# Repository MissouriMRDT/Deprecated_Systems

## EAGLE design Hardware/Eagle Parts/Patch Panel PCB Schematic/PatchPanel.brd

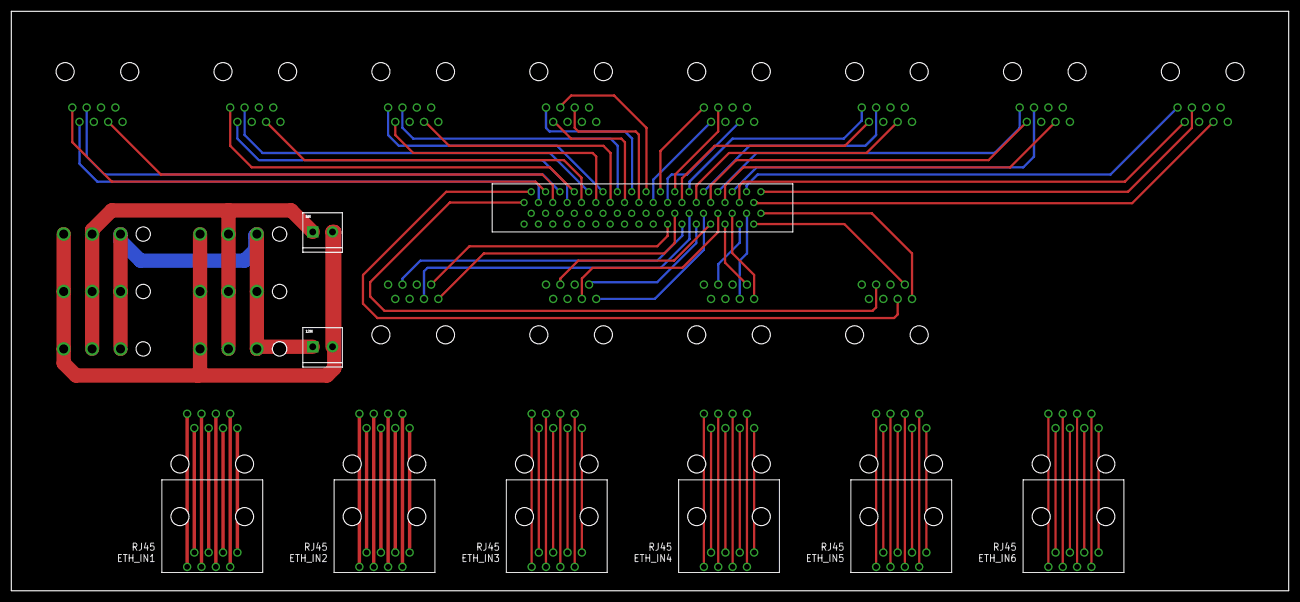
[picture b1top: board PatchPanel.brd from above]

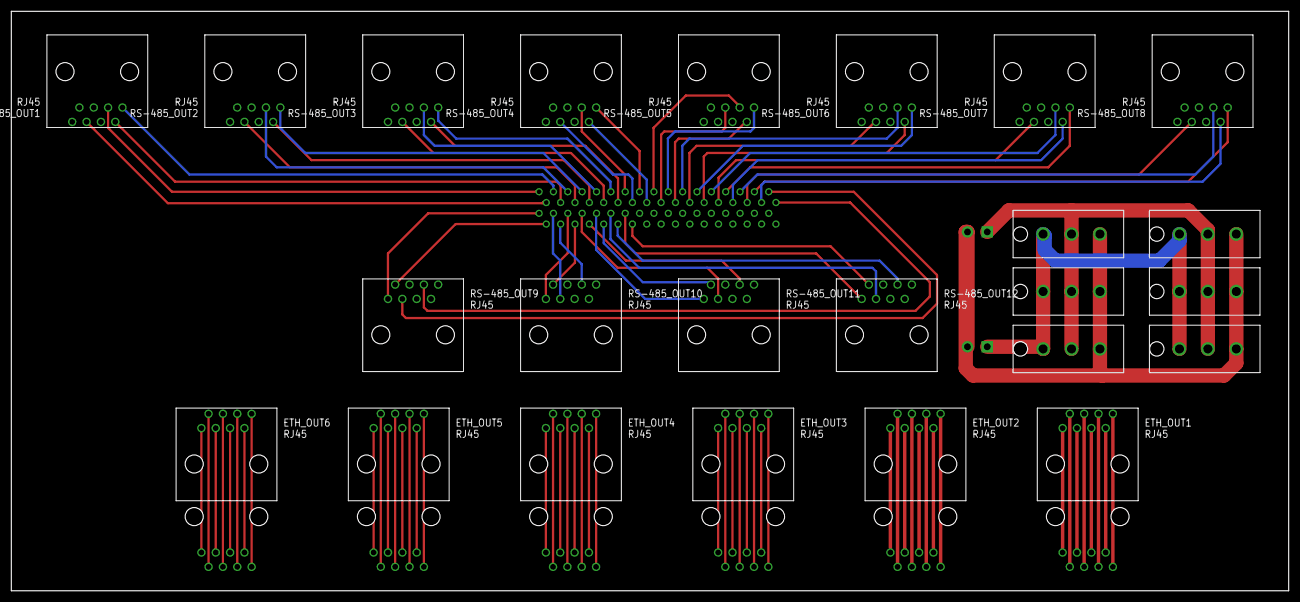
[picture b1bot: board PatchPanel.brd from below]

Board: 2 copper layers, 226.0 x 102.5 mm, 33 parts (24 on the bottom side), 99 nets.

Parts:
5IN, 12IN: M023.5MM; SCREWTERMINAL-3.5MM-2
ETH_IN1, ETH_IN2, ETH_IN3, ETH_IN4, ETH_IN5, ETH_IN6: RJ45; RJ45-CAT5E
ETH_OUT1, ETH_OUT2, ETH_OUT3, ETH_OUT4, ETH_OUT5, ETH_OUT6: RJ45; RJ45-CAT5E
RS-485_OUT1, RS-485_OUT2, RS-485_OUT3, RS-485_OUT4, RS-485_OUT5, RS-485_OUT6, RS-485_OUT7, RS-485_OUT8, RS-485_OUT9, RS-485_OUT10, RS-485_OUT11, RS-485_OUT12: RJ45; RJ45-CAT5E
U$1: TB60050685100; 60050685100
U$2, U$3, U$4, U$5, U$6, U$7: 3PIN; 0.93"

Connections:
1_RX+: RS-485_OUT1.1, U$1.3
1_RX-: RS-485_OUT1.2, U$1.4
1_TX+: RS-485_OUT1.3, U$1.1
1_TX-: RS-485_OUT1.6, U$1.2
2_RX+: RS-485_OUT2.1, U$1.7
2_RX-: RS-485_OUT2.2, U$1.8
2_TX+: RS-485_OUT2.3, U$1.5
2_TX-: RS-485_OUT2.6, U$1.6
3_RX+: RS-485_OUT3.1, U$1.11
3_RX-: RS-485_OUT3.2, U$1.12
3_TX+: RS-485_OUT3.3, U$1.9
3_TX-: RS-485_OUT3.6, U$1.10
4_RX+: RS-485_OUT4.1, U$1.15
4_RX-: RS-485_OUT4.2, U$1.16
4_TX+: RS-485_OUT4.3, U$1.13
4_TX-: RS-485_OUT4.6, U$1.14
5_RX+: RS-485_OUT5.1, U$1.19
5_RX-: RS-485_OUT5.2, U$1.20
5_TX+: RS-485_OUT5.3, U$1.17
5_TX-: RS-485_OUT5.5, U$1.18
6_RX+: RS-485_OUT6.1, U$1.23
6_RX-: RS-485_OUT6.2, U$1.24
6_TX+: RS-485_OUT6.3, U$1.21
6_TX-: RS-485_OUT6.6, U$1.22
7_RX+: RS-485_OUT7.1, U$1.27
7_RX-: RS-485_OUT7.2, U$1.28
7_TX+: RS-485_OUT7.3, U$1.25
7_TX-: RS-485_OUT7.6, U$1.26
8_RX+: RS-485_OUT8.1, U$1.31
8_RX-: RS-485_OUT8.2, U$1.32
8_TX+: RS-485_OUT8.3, U$1.29
8_TX-: RS-485_OUT8.6, U$1.30
9_RX+: RS-485_OUT9.1, U$1.35
9_RX-: RS-485_OUT9.2, U$1.36
9_TX+: RS-485_OUT9.3, U$1.33
9_TX-: RS-485_OUT9.6, U$1.34
10_RX+: RS-485_OUT10.1, U$1.39
10_RX-: RS-485_OUT10.2, U$1.40
10_TX+: RS-485_OUT10.3, U$1.37
10_TX-: RS-485_OUT10.6, U$1.38
11_RX+: RS-485_OUT11.1, U$1.43
11_RX-: RS-485_OUT11.2, U$1.44
11_TX+: RS-485_OUT11.3, U$1.41
11_TX-: RS-485_OUT11.6, U$1.42
12_RX+: RS-485_OUT12.1, U$1.47
12_RX-: RS-485_OUT12.2, U$1.48
12_TX+: RS-485_OUT12.3, U$1.45
12_TX-: RS-485_OUT12.6, U$1.46
+5V: 5IN.1, U$2.2, U$3.2, U$4.2, U$5.2, U$6.2, U$7.2
+12V: 12IN.1, U$2.1, U$3.1, U$4.1, U$5.1, U$6.1, U$7.1
GND: 5IN.2, 12IN.2, U$2.3, U$3.3, U$4.3, U$5.3, U$6.3, U$7.3
unnamed: ETH_IN1.1, ETH_OUT1.1
unnamed: ETH_IN1.2, ETH_OUT1.2
unnamed: ETH_IN1.3, ETH_OUT1.3
unnamed: ETH_IN1.4, ETH_OUT1.4
unnamed: ETH_IN1.5, ETH_OUT1.5
unnamed: ETH_IN1.6, ETH_OUT1.6
unnamed: ETH_IN1.7, ETH_OUT1.7
unnamed: ETH_IN1.8, ETH_OUT1.8
unnamed: ETH_IN2.1, ETH_OUT2.1
unnamed: ETH_IN2.2, ETH_OUT2.2
unnamed: ETH_IN2.3, ETH_OUT2.3
unnamed: ETH_IN2.4, ETH_OUT2.4
unnamed: ETH_IN2.5, ETH_OUT2.5
unnamed: ETH_IN2.6, ETH_OUT2.6
unnamed: ETH_IN2.7, ETH_OUT2.7
unnamed: ETH_IN2.8, ETH_OUT2.8
unnamed: ETH_IN3.1, ETH_OUT3.1
unnamed: ETH_IN3.2, ETH_OUT3.2
unnamed: ETH_IN3.3, ETH_OUT3.3
unnamed: ETH_IN3.4, ETH_OUT3.4
unnamed: ETH_IN3.5, ETH_OUT3.5
unnamed: ETH_IN3.6, ETH_OUT3.6
unnamed: ETH_IN3.7, ETH_OUT3.7
unnamed: ETH_IN3.8, ETH_OUT3.8
unnamed: ETH_IN4.8, ETH_OUT4.8
unnamed: ETH_IN4.7, ETH_OUT4.7
unnamed: ETH_IN4.6, ETH_OUT4.6
unnamed: ETH_IN4.5, ETH_OUT4.5
unnamed: ETH_IN4.4, ETH_OUT4.4
unnamed: ETH_IN4.3, ETH_OUT4.3
unnamed: ETH_IN4.2, ETH_OUT4.2
unnamed: ETH_IN4.1, ETH_OUT4.1
unnamed: ETH_IN5.8, ETH_OUT5.8
unnamed: ETH_IN5.7, ETH_OUT5.7
unnamed: ETH_IN5.6, ETH_OUT5.6
unnamed: ETH_IN5.5, ETH_OUT5.5
unnamed: ETH_IN5.4, ETH_OUT5.4
unnamed: ETH_IN5.3, ETH_OUT5.3
unnamed: ETH_IN5.2, ETH_OUT5.2
unnamed: ETH_IN5.1, ETH_OUT5.1
unnamed: ETH_IN6.1, ETH_OUT6.1
unnamed: ETH_IN6.2, ETH_OUT6.2
unnamed: ETH_IN6.3, ETH_OUT6.3
unnamed: ETH_IN6.4, ETH_OUT6.4
unnamed: ETH_IN6.5, ETH_OUT6.5
unnamed: ETH_IN6.6, ETH_OUT6.6
unnamed: ETH_IN6.7, ETH_OUT6.7
unnamed: ETH_IN6.8, ETH_OUT6.8

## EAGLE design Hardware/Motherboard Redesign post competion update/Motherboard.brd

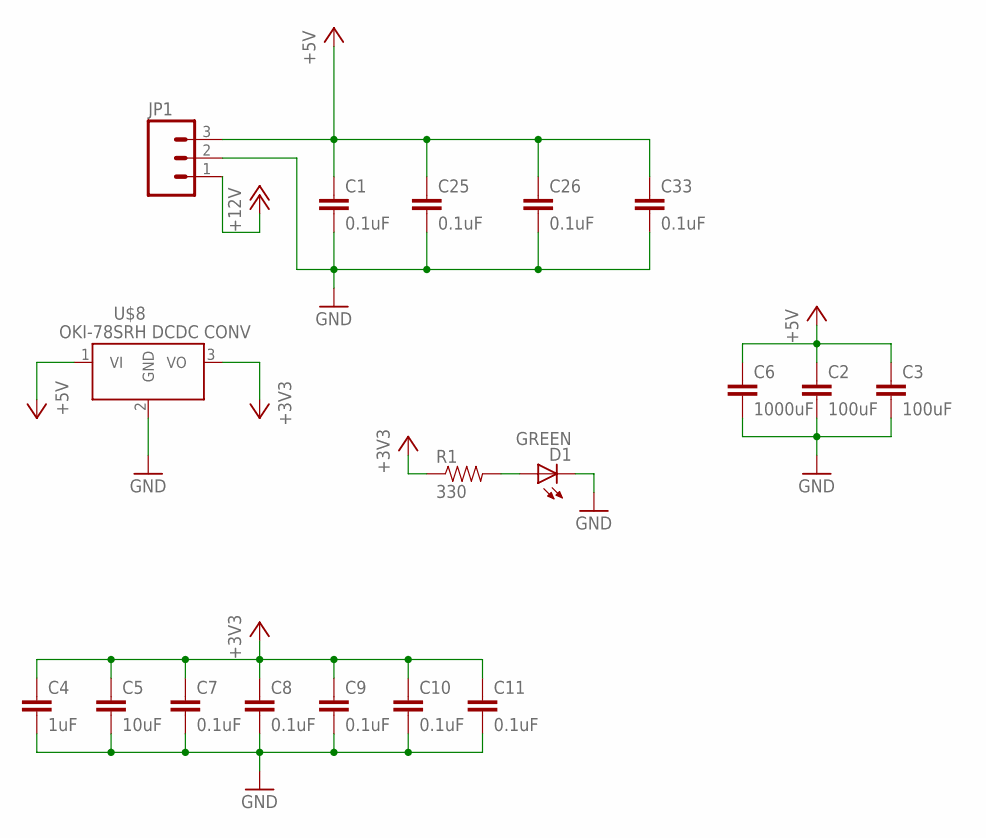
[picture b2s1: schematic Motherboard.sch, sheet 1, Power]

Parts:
C1, C7, C8, C9, C10, C11, C25, C26, C33: 0.1uF; 1206
C2, C3: 100uF; 1206
C4: 1uF; 1206
C5: 10uF; 1206
C6: 1000uF; 1206
D1: GREEN; LED-1206
JP1: M03SCREW; SCREWTERMINAL-3.5MM-3
R1: 330; 1206
U$8: Q_OKI-78SR; OKI-78SRH

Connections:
5V: C1.1, C2.1, C3.1, C6.1, C25.1, C26.1, C33.1, JP1.3, U$8.1 (VI); also elsewhere on the board
+3V3: C4.1, C5.1, C7.1, C8.1, C9.1, C10.1, C11.1, R1.1, U$8.3 (VO); also elsewhere on the board
+12V: JP1.1; also elsewhere on the board
GND: C1.2, C2.2, C3.2, C4.2, C5.2, C6.2, C7.2, C8.2, C9.2, C10.2, C11.2, C25.2, C26.2, C33.2, D1.C, JP1.2, U$8.2 (GND); also elsewhere on the board
unnamed: D1.A, R1.2

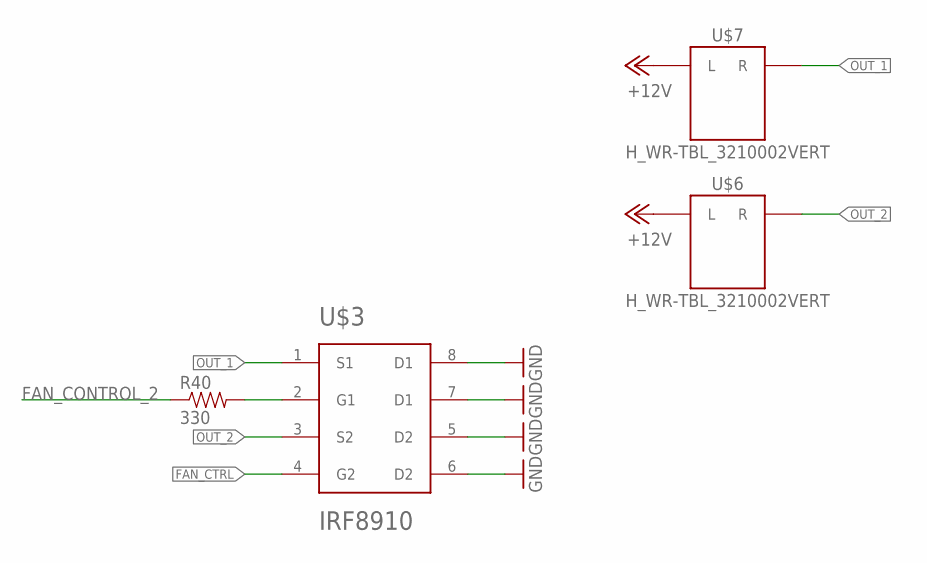
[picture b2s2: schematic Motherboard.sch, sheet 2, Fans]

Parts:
R40: 330; 1206
U$3: IRF8910; SO8
U$6, U$7: H_WR-TBL_3210002VERT; 691321100002

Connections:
+12V: U$6.L, U$7.L; also elsewhere on the board
FAN_CONTROL_2: R40.1; also elsewhere on the board
FAN_CTRL: R40.2, U$3.2 (G1), U$3.4 (G2)
GND: U$3.5 (D2), U$3.6 (D2), U$3.7 (D1), U$3.8 (D1); also elsewhere on the board
OUT_1: U$3.1 (S1), U$7.R
OUT_2: U$3.3 (S2), U$6.R

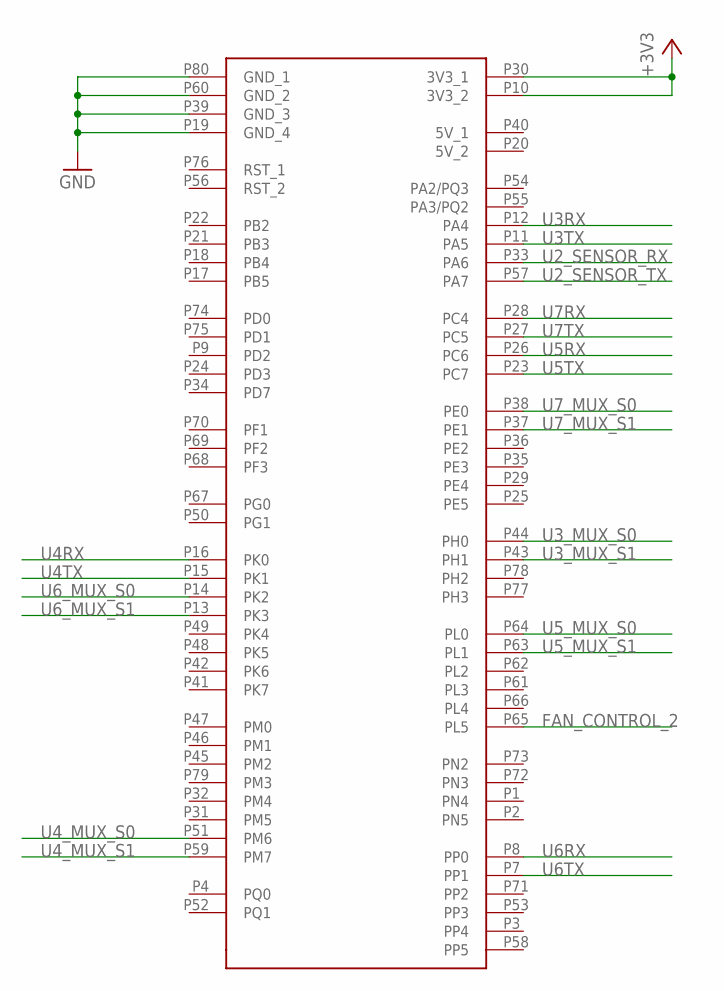
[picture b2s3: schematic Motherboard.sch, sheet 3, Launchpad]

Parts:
U$5: STELLARISLAUNCHPAD_CONNECTED

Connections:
+3V3: U$5.P10 (3V3_2), U$5.P30 (3V3_1); also elsewhere on the board
FAN_CONTROL_2: U$5.P65 (PL5); also elsewhere on the board
GND: U$5.P19 (GND_4), U$5.P39 (GND_3), U$5.P60 (GND_2), U$5.P80 (GND_1); also elsewhere on the board
U2_SENSOR_RX: U$5.P33 (PA6); also elsewhere on the board
U2_SENSOR_TX: U$5.P57 (PA7); also elsewhere on the board
U3RX: U$5.P12 (PA4); also elsewhere on the board
U3TX: U$5.P11 (PA5); also elsewhere on the board
U3_MUX_S0: U$5.P44 (PH0); also elsewhere on the board
U3_MUX_S1: U$5.P43 (PH1); also elsewhere on the board
U4RX: U$5.P16 (PK0); also elsewhere on the board
U4TX: U$5.P15 (PK1); also elsewhere on the board
U4_MUX_S0: U$5.P51 (PM6); also elsewhere on the board
U4_MUX_S1: U$5.P59 (PM7); also elsewhere on the board
U5RX: U$5.P26 (PC6); also elsewhere on the board
U5TX: U$5.P23 (PC7); also elsewhere on the board
U5_MUX_S0: U$5.P64 (PL0); also elsewhere on the board
U5_MUX_S1: U$5.P63 (PL1); also elsewhere on the board
U6RX: U$5.P8 (PP0); also elsewhere on the board
U6TX: U$5.P7 (PP1); also elsewhere on the board
U6_MUX_S0: U$5.P14 (PK2); also elsewhere on the board
U6_MUX_S1: U$5.P13 (PK3); also elsewhere on the board
U7RX: U$5.P28 (PC4); also elsewhere on the board
U7TX: U$5.P27 (PC5); also elsewhere on the board
U7_MUX_S0: U$5.P38 (PE0); also elsewhere on the board
U7_MUX_S1: U$5.P37 (PE1); also elsewhere on the board

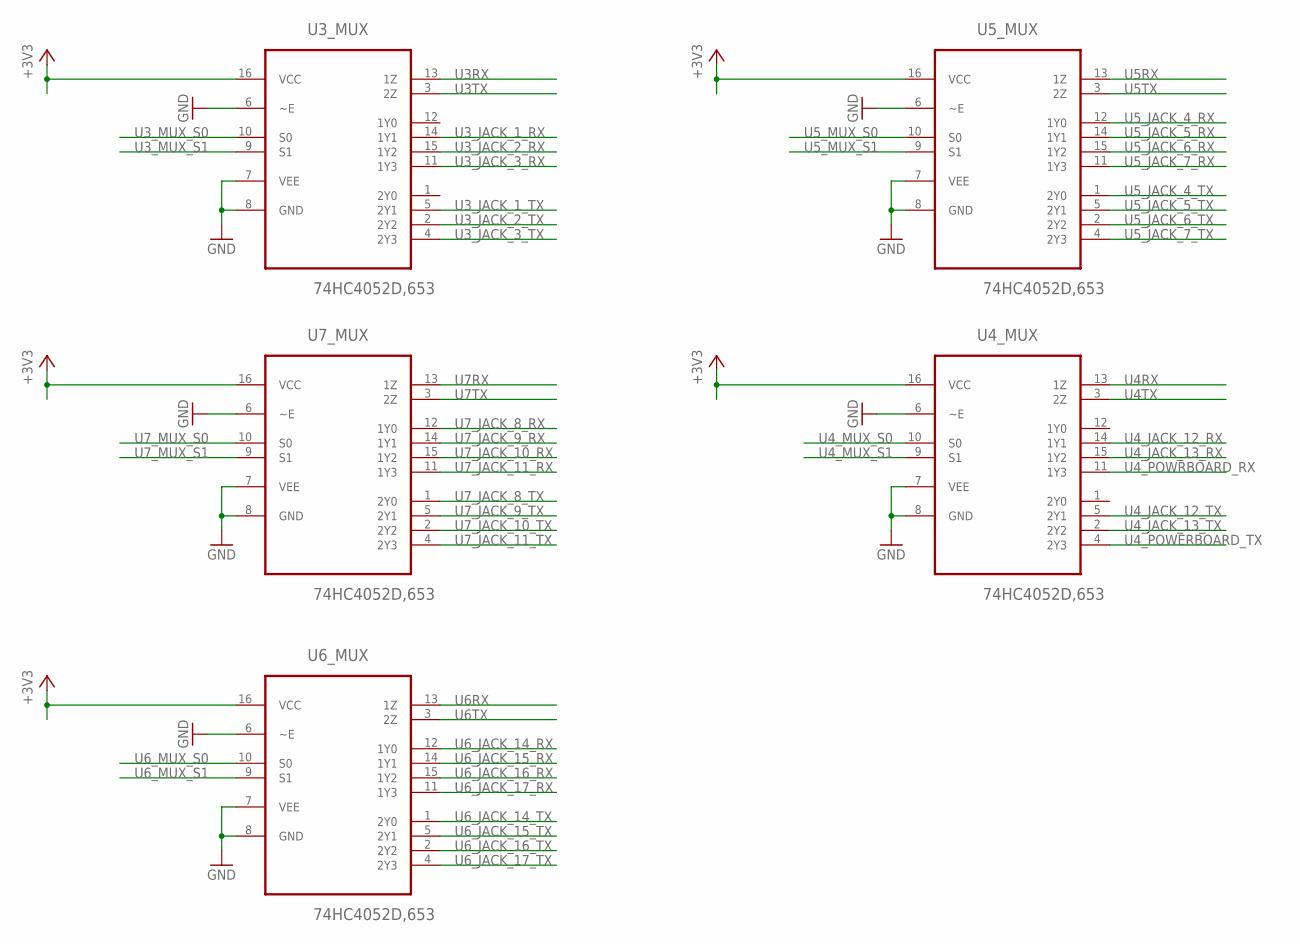
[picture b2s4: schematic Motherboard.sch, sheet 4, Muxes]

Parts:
U3_MUX, U4_MUX, U5_MUX, U6_MUX, U7_MUX: 74HC4052D,653; SOIC127P600X175-16N

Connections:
+3V3: U3_MUX.16 (VCC), U4_MUX.16 (VCC), U5_MUX.16 (VCC), U6_MUX.16 (VCC), U7_MUX.16 (VCC); also elsewhere on the board
GND: U3_MUX.6 (~E), U3_MUX.7 (VEE), U3_MUX.8 (GND), U4_MUX.6 (~E), U4_MUX.7 (VEE), U4_MUX.8 (GND), U5_MUX.6 (~E), U5_MUX.7 (VEE), U5_MUX.8 (GND), U6_MUX.6 (~E), U6_MUX.7 (VEE), U6_MUX.8 (GND), U7_MUX.6 (~E), U7_MUX.7 (VEE), U7_MUX.8 (GND); also elsewhere on the board
U3RX: U3_MUX.13 (1Z); also elsewhere on the board
U3TX: U3_MUX.3 (2Z); also elsewhere on the board
U3_JACK_1_RX: U3_MUX.14 (1Y1); also elsewhere on the board
U3_JACK_1_TX: U3_MUX.5 (2Y1); also elsewhere on the board
U3_JACK_2_RX: U3_MUX.15 (1Y2); also elsewhere on the board
U3_JACK_2_TX: U3_MUX.2 (2Y2); also elsewhere on the board
U3_JACK_3_RX: U3_MUX.11 (1Y3); also elsewhere on the board
U3_JACK_3_TX: U3_MUX.4 (2Y3); also elsewhere on the board
U3_MUX_S0: U3_MUX.10 (S0); also elsewhere on the board
U3_MUX_S1: U3_MUX.9 (S1); also elsewhere on the board
U4RX: U4_MUX.13 (1Z); also elsewhere on the board
U4TX: U4_MUX.3 (2Z); also elsewhere on the board
U4_JACK_12_RX: U4_MUX.14 (1Y1); also elsewhere on the board
U4_JACK_12_TX: U4_MUX.5 (2Y1); also elsewhere on the board
U4_JACK_13_RX: U4_MUX.15 (1Y2); also elsewhere on the board
U4_JACK_13_TX: U4_MUX.2 (2Y2); also elsewhere on the board
U4_MUX_S0: U4_MUX.10 (S0); also elsewhere on the board
U4_MUX_S1: U4_MUX.9 (S1); also elsewhere on the board
U4_POWERBOARD_TX: U4_MUX.4 (2Y3); also elsewhere on the board
U4_POWRBOARD_RX: U4_MUX.11 (1Y3); also elsewhere on the board
U5RX: U5_MUX.13 (1Z); also elsewhere on the board
U5TX: U5_MUX.3 (2Z); also elsewhere on the board
U5_JACK_4_RX: U5_MUX.12 (1Y0); also elsewhere on the board
U5_JACK_4_TX: U5_MUX.1 (2Y0); also elsewhere on the board
U5_JACK_5_RX: U5_MUX.14 (1Y1); also elsewhere on the board
U5_JACK_5_TX: U5_MUX.5 (2Y1); also elsewhere on the board
U5_JACK_6_RX: U5_MUX.15 (1Y2); also elsewhere on the board
U5_JACK_6_TX: U5_MUX.2 (2Y2); also elsewhere on the board
U5_JACK_7_RX: U5_MUX.11 (1Y3); also elsewhere on the board
U5_JACK_7_TX: U5_MUX.4 (2Y3); also elsewhere on the board
U5_MUX_S0: U5_MUX.10 (S0); also elsewhere on the board
U5_MUX_S1: U5_MUX.9 (S1); also elsewhere on the board
U6RX: U6_MUX.13 (1Z); also elsewhere on the board
U6TX: U6_MUX.3 (2Z); also elsewhere on the board
U6_JACK_14_RX: U6_MUX.12 (1Y0); also elsewhere on the board
U6_JACK_14_TX: U6_MUX.1 (2Y0); also elsewhere on the board
U6_JACK_15_RX: U6_MUX.14 (1Y1); also elsewhere on the board
U6_JACK_15_TX: U6_MUX.5 (2Y1); also elsewhere on the board
U6_JACK_16_RX: U6_MUX.15 (1Y2); also elsewhere on the board
U6_JACK_16_TX: U6_MUX.2 (2Y2); also elsewhere on the board
U6_JACK_17_RX: U6_MUX.11 (1Y3); also elsewhere on the board
U6_JACK_17_TX: U6_MUX.4 (2Y3); also elsewhere on the board
U6_MUX_S0: U6_MUX.10 (S0); also elsewhere on the board
U6_MUX_S1: U6_MUX.9 (S1); also elsewhere on the board
U7RX: U7_MUX.13 (1Z); also elsewhere on the board
U7TX: U7_MUX.3 (2Z); also elsewhere on the board
U7_JACK_8_RX: U7_MUX.12 (1Y0); also elsewhere on the board
U7_JACK_8_TX: U7_MUX.1 (2Y0); also elsewhere on the board
U7_JACK_9_RX: U7_MUX.14 (1Y1); also elsewhere on the board
U7_JACK_9_TX: U7_MUX.5 (2Y1); also elsewhere on the board
U7_JACK_10_RX: U7_MUX.15 (1Y2); also elsewhere on the board
U7_JACK_10_TX: U7_MUX.2 (2Y2); also elsewhere on the board
U7_JACK_11_RX: U7_MUX.11 (1Y3); also elsewhere on the board
U7_JACK_11_TX: U7_MUX.4 (2Y3); also elsewhere on the board
U7_MUX_S0: U7_MUX.10 (S0); also elsewhere on the board
U7_MUX_S1: U7_MUX.9 (S1); also elsewhere on the board

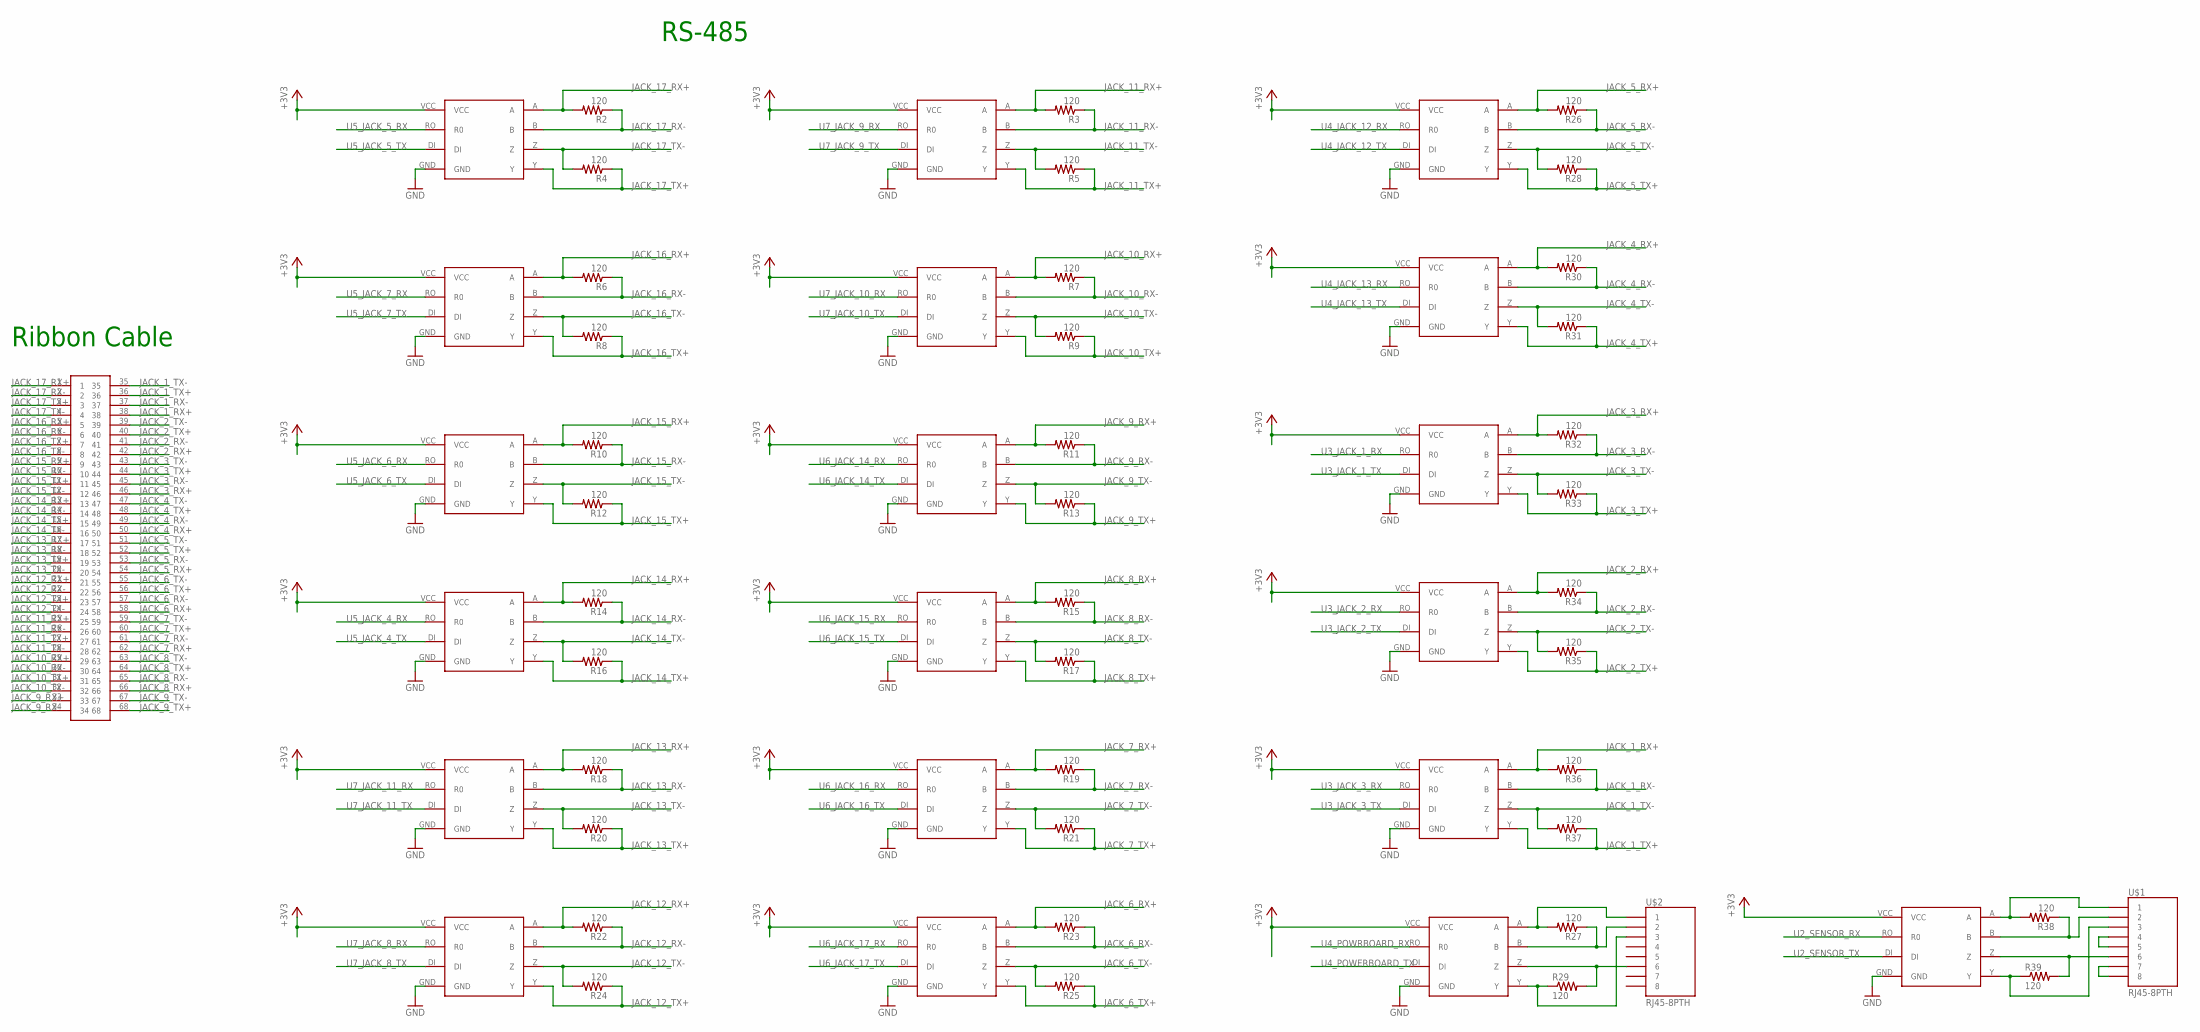
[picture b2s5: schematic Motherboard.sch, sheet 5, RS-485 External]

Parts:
R2, R3, R4, R5, R6, R7, R8, R9, R10, R11, R12, R13, R14, R15, R16, R17, R18, R19, R20, R21, R22, R23, R24, R25, R26, R27, R28, R29, R30, R31, R32, R33, R34, R35, R36, R37, R38, R39: 120; 1206
RS-485-1, RS-485-2: MAX3077; MAX3070E
RS_TRANS_1, RS_TRANS_2, RS_TRANS_3, RS_TRANS_4, RS_TRANS_5, RS_TRANS_6, RS_TRANS_7, RS_TRANS_8, RS_TRANS_9, RS_TRANS_10, RS_TRANS_11, RS_TRANS_12, RS_TRANS_13, RS_TRANS_14, RS_TRANS_15, RS_TRANS_16, RS_TRANS_17: MAX3077; MAX3070E
U$1, U$2: RJ45-8PTH; RJ45-8
U$4: TB60050685100; 60050685100

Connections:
5V: U$1.4, U$1.5; also elsewhere on the board
18_RX+: R27.2, RS-485-2.A, U$2.1
18_RX+1: R38.2, RS-485-1.A, U$1.1
18_RX-: R27.1, RS-485-2.B, U$2.2
18_RX-1: R38.1, RS-485-1.B, U$1.2
18_TX+: R29.1, RS-485-2.Y, U$2.3
18_TX+1: R39.1, RS-485-1.Y, U$1.3
18_TX-: R29.2, RS-485-2.Z, U$2.6
18_TX-1: R39.2, RS-485-1.Z, U$1.6
+3V3: RS-485-1.VCC, RS-485-2.VCC, RS_TRANS_1.VCC, RS_TRANS_2.VCC, RS_TRANS_3.VCC, RS_TRANS_4.VCC, RS_TRANS_5.VCC, RS_TRANS_6.VCC, RS_TRANS_7.VCC, RS_TRANS_8.VCC, RS_TRANS_9.VCC, RS_TRANS_10.VCC, RS_TRANS_11.VCC, RS_TRANS_12.VCC, RS_TRANS_13.VCC, RS_TRANS_14.VCC, RS_TRANS_15.VCC, RS_TRANS_16.VCC, RS_TRANS_17.VCC; also elsewhere on the board
GND: RS-485-1.GND, RS-485-2.GND, RS_TRANS_1.GND, RS_TRANS_2.GND, RS_TRANS_3.GND, RS_TRANS_4.GND, RS_TRANS_5.GND, RS_TRANS_6.GND, RS_TRANS_7.GND, RS_TRANS_8.GND, RS_TRANS_9.GND, RS_TRANS_10.GND, RS_TRANS_11.GND, RS_TRANS_12.GND, RS_TRANS_13.GND, RS_TRANS_14.GND, RS_TRANS_15.GND, RS_TRANS_16.GND, RS_TRANS_17.GND, U$1.7, U$1.8; also elsewhere on the board
JACK_1_RX+: R36.2, RS_TRANS_17.A, U$4.38
JACK_1_RX-: R36.1, RS_TRANS_17.B, U$4.37
JACK_1_TX+: R37.1, RS_TRANS_17.Y, U$4.36
JACK_1_TX-: R37.2, RS_TRANS_17.Z, U$4.35
JACK_2_RX+: R34.2, RS_TRANS_16.A, U$4.42
JACK_2_RX-: R34.1, RS_TRANS_16.B, U$4.41
JACK_2_TX+: R35.1, RS_TRANS_16.Y, U$4.40
JACK_2_TX-: R35.2, RS_TRANS_16.Z, U$4.39
JACK_3_RX+: R32.2, RS_TRANS_15.A, U$4.46
JACK_3_RX-: R32.1, RS_TRANS_15.B, U$4.45
JACK_3_TX+: R33.1, RS_TRANS_15.Y, U$4.44
JACK_3_TX-: R33.2, RS_TRANS_15.Z, U$4.43
JACK_4_RX+: R30.2, RS_TRANS_14.A, U$4.50
JACK_4_RX-: R30.1, RS_TRANS_14.B, U$4.49
JACK_4_TX+: R31.1, RS_TRANS_14.Y, U$4.48
JACK_4_TX-: R31.2, RS_TRANS_14.Z, U$4.47
JACK_5_RX+: R26.2, RS_TRANS_13.A, U$4.54
JACK_5_RX-: R26.1, RS_TRANS_13.B, U$4.53
JACK_5_TX+: R28.1, RS_TRANS_13.Y, U$4.52
JACK_5_TX-: R28.2, RS_TRANS_13.Z, U$4.51
JACK_6_RX+: R23.2, RS_TRANS_12.A, U$4.58
JACK_6_RX-: R23.1, RS_TRANS_12.B, U$4.57
JACK_6_TX+: R25.1, RS_TRANS_12.Y, U$4.56
JACK_6_TX-: R25.2, RS_TRANS_12.Z, U$4.55
JACK_7_RX+: R19.2, RS_TRANS_10.A, U$4.62
JACK_7_RX-: R19.1, RS_TRANS_10.B, U$4.61
JACK_7_TX+: R21.1, RS_TRANS_10.Y, U$4.60
JACK_7_TX-: R21.2, RS_TRANS_10.Z, U$4.59
JACK_8_RX+: R15.2, RS_TRANS_8.A, U$4.66
JACK_8_RX-: R15.1, RS_TRANS_8.B, U$4.65
JACK_8_TX+: R17.1, RS_TRANS_8.Y, U$4.64
JACK_8_TX-: R17.2, RS_TRANS_8.Z, U$4.63
JACK_9_RX+: R11.2, RS_TRANS_6.A, U$4.33
JACK_9_RX-: R11.1, RS_TRANS_6.B, U$4.34
JACK_9_TX+: R13.1, RS_TRANS_6.Y, U$4.68
JACK_9_TX-: R13.2, RS_TRANS_6.Z, U$4.67
JACK_10_RX+: R7.2, RS_TRANS_4.A, U$4.29
JACK_10_RX-: R7.1, RS_TRANS_4.B, U$4.30
JACK_10_TX+: R9.1, RS_TRANS_4.Y, U$4.31
JACK_10_TX-: R9.2, RS_TRANS_4.Z, U$4.32
JACK_11_RX+: R3.2, RS_TRANS_2.A, U$4.25
JACK_11_RX-: R3.1, RS_TRANS_2.B, U$4.26
JACK_11_TX+: R5.1, RS_TRANS_2.Y, U$4.27
JACK_11_TX-: R5.2, RS_TRANS_2.Z, U$4.28
JACK_12_RX+: R22.2, RS_TRANS_11.A, U$4.21
JACK_12_RX-: R22.1, RS_TRANS_11.B, U$4.22
JACK_12_TX+: R24.1, RS_TRANS_11.Y, U$4.23
JACK_12_TX-: R24.2, RS_TRANS_11.Z, U$4.24
JACK_13_RX+: R18.2, RS_TRANS_9.A, U$4.17
JACK_13_RX-: R18.1, RS_TRANS_9.B, U$4.18
JACK_13_TX+: R20.1, RS_TRANS_9.Y, U$4.19
JACK_13_TX-: R20.2, RS_TRANS_9.Z, U$4.20
JACK_14_RX+: R14.2, RS_TRANS_7.A, U$4.13
JACK_14_RX-: R14.1, RS_TRANS_7.B, U$4.14
JACK_14_TX+: R16.1, RS_TRANS_7.Y, U$4.15
JACK_14_TX-: R16.2, RS_TRANS_7.Z, U$4.16
JACK_15_RX+: R10.2, RS_TRANS_5.A, U$4.9
JACK_15_RX-: R10.1, RS_TRANS_5.B, U$4.10
JACK_15_TX+: R12.1, RS_TRANS_5.Y, U$4.11
JACK_15_TX-: R12.2, RS_TRANS_5.Z, U$4.12
JACK_16_RX+: R6.2, RS_TRANS_3.A, U$4.5
JACK_16_RX-: R6.1, RS_TRANS_3.B, U$4.6
JACK_16_TX+: R8.1, RS_TRANS_3.Y, U$4.7
JACK_16_TX-: R8.2, RS_TRANS_3.Z, U$4.8
JACK_17_RX+: R2.2, RS_TRANS_1.A, U$4.1
JACK_17_RX-: R2.1, RS_TRANS_1.B, U$4.2
JACK_17_TX+: R4.1, RS_TRANS_1.Y, U$4.3
JACK_17_TX-: R4.2, RS_TRANS_1.Z, U$4.4
U2_SENSOR_RX: RS-485-1.RO (R0); also elsewhere on the board
U2_SENSOR_TX: RS-485-1.DI; also elsewhere on the board
U3_JACK_1_RX: RS_TRANS_15.RO (R0); also elsewhere on the board
U3_JACK_1_TX: RS_TRANS_15.DI; also elsewhere on the board
U3_JACK_2_RX: RS_TRANS_16.RO (R0); also elsewhere on the board
U3_JACK_2_TX: RS_TRANS_16.DI; also elsewhere on the board
U3_JACK_3_RX: RS_TRANS_17.RO (R0); also elsewhere on the board
U3_JACK_3_TX: RS_TRANS_17.DI; also elsewhere on the board
U4_JACK_12_RX: RS_TRANS_13.RO (R0); also elsewhere on the board
U4_JACK_12_TX: RS_TRANS_13.DI; also elsewhere on the board
U4_JACK_13_RX: RS_TRANS_14.RO (R0); also elsewhere on the board
U4_JACK_13_TX: RS_TRANS_14.DI; also elsewhere on the board
U4_POWERBOARD_TX: RS-485-2.DI; also elsewhere on the board
U4_POWRBOARD_RX: RS-485-2.RO (R0); also elsewhere on the board
U5_JACK_4_RX: RS_TRANS_7.RO (R0); also elsewhere on the board
U5_JACK_4_TX: RS_TRANS_7.DI; also elsewhere on the board
U5_JACK_5_RX: RS_TRANS_1.RO (R0); also elsewhere on the board
U5_JACK_5_TX: RS_TRANS_1.DI; also elsewhere on the board
U5_JACK_6_RX: RS_TRANS_5.RO (R0); also elsewhere on the board
U5_JACK_6_TX: RS_TRANS_5.DI; also elsewhere on the board
U5_JACK_7_RX: RS_TRANS_3.RO (R0); also elsewhere on the board
U5_JACK_7_TX: RS_TRANS_3.DI; also elsewhere on the board
U6_JACK_14_RX: RS_TRANS_6.RO (R0); also elsewhere on the board
U6_JACK_14_TX: RS_TRANS_6.DI; also elsewhere on the board
U6_JACK_15_RX: RS_TRANS_8.RO (R0); also elsewhere on the board
U6_JACK_15_TX: RS_TRANS_8.DI; also elsewhere on the board
U6_JACK_16_RX: RS_TRANS_10.RO (R0); also elsewhere on the board
U6_JACK_16_TX: RS_TRANS_10.DI; also elsewhere on the board
U6_JACK_17_RX: RS_TRANS_12.RO (R0); also elsewhere on the board
U6_JACK_17_TX: RS_TRANS_12.DI; also elsewhere on the board
U7_JACK_8_RX: RS_TRANS_11.RO (R0); also elsewhere on the board
U7_JACK_8_TX: RS_TRANS_11.DI; also elsewhere on the board
U7_JACK_9_RX: RS_TRANS_2.RO (R0); also elsewhere on the board
U7_JACK_9_TX: RS_TRANS_2.DI; also elsewhere on the board
U7_JACK_10_RX: RS_TRANS_4.RO (R0); also elsewhere on the board
U7_JACK_10_TX: RS_TRANS_4.DI; also elsewhere on the board
U7_JACK_11_RX: RS_TRANS_9.RO (R0); also elsewhere on the board
U7_JACK_11_TX: RS_TRANS_9.DI; also elsewhere on the board

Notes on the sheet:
Ribbon Cable
RS-485

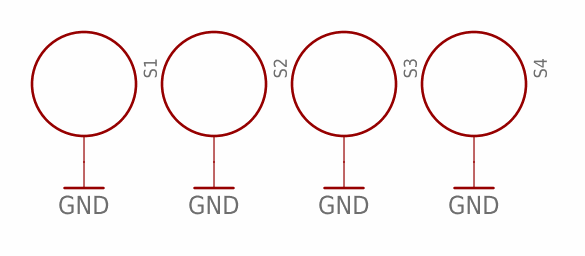
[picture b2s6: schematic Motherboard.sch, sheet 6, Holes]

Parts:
S1, S2, S3, S4: STANDOFF_ELECTRICAL; STANDOFF-ELECTRICAL

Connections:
GND: S1.P1, S2.P1, S3.P1, S4.P1; also elsewhere on the board

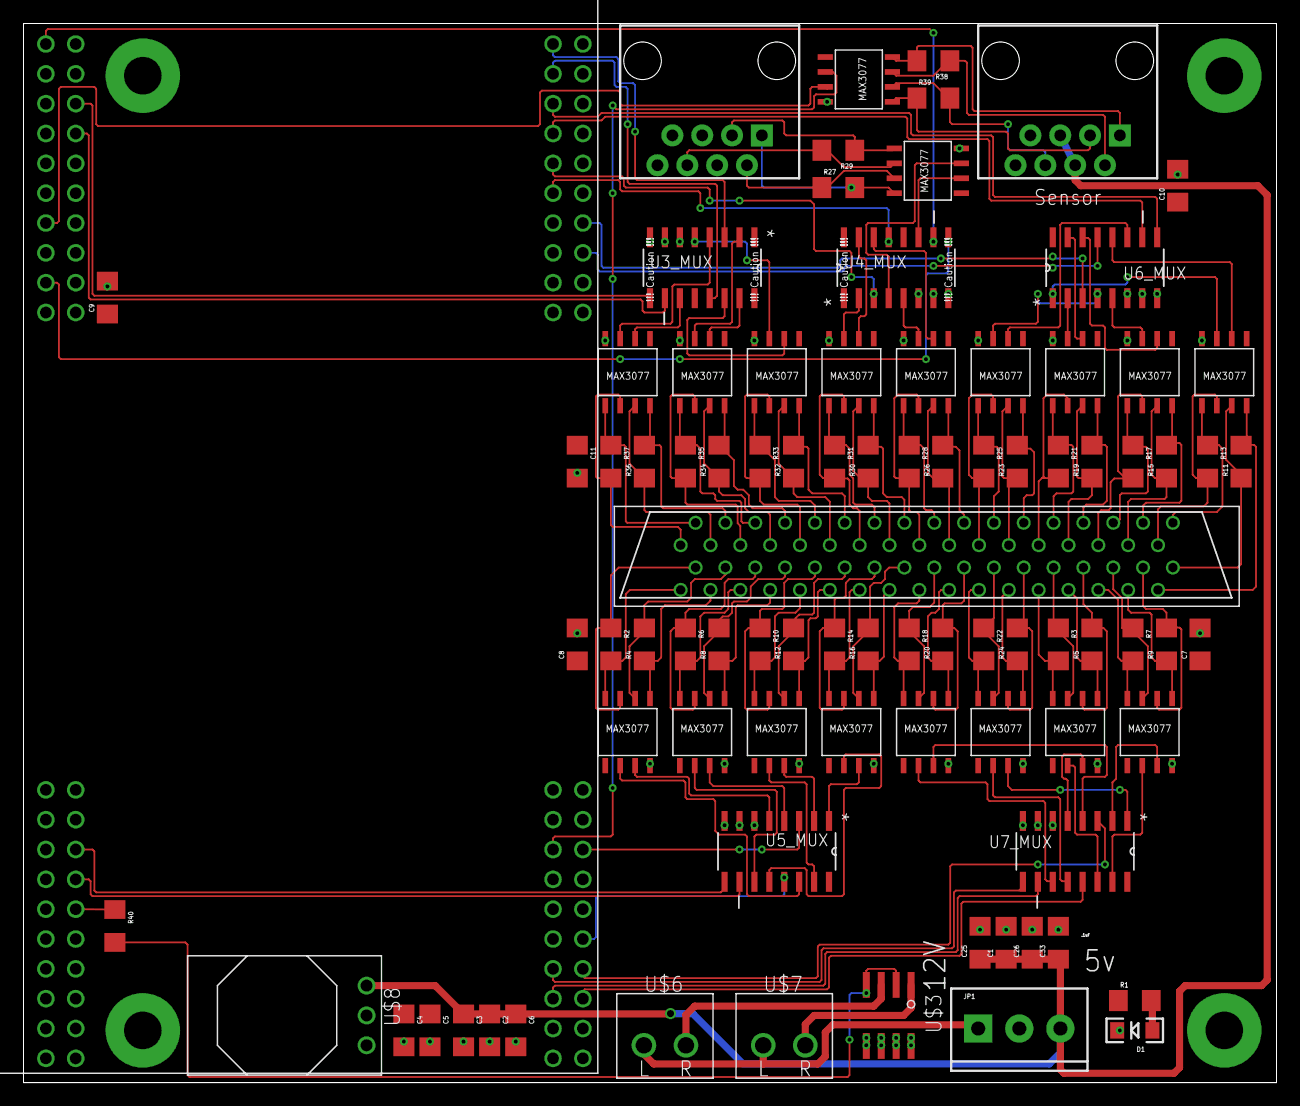
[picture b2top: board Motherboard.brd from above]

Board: 2 copper layers, 106.7 x 90.2 mm, 92 parts (0 on the bottom side), 143 nets.

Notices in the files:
parts and their libraries:
SparkFun-Connectors: Licensing: CC v3.0 Share-Alike You are welcome to use this library for commercial purposes.
SparkFun-Electromechanical: Licensing: Creative Commons ShareAlike 4.0 International - https://creativecommons.org/licenses/by-sa/4.0
